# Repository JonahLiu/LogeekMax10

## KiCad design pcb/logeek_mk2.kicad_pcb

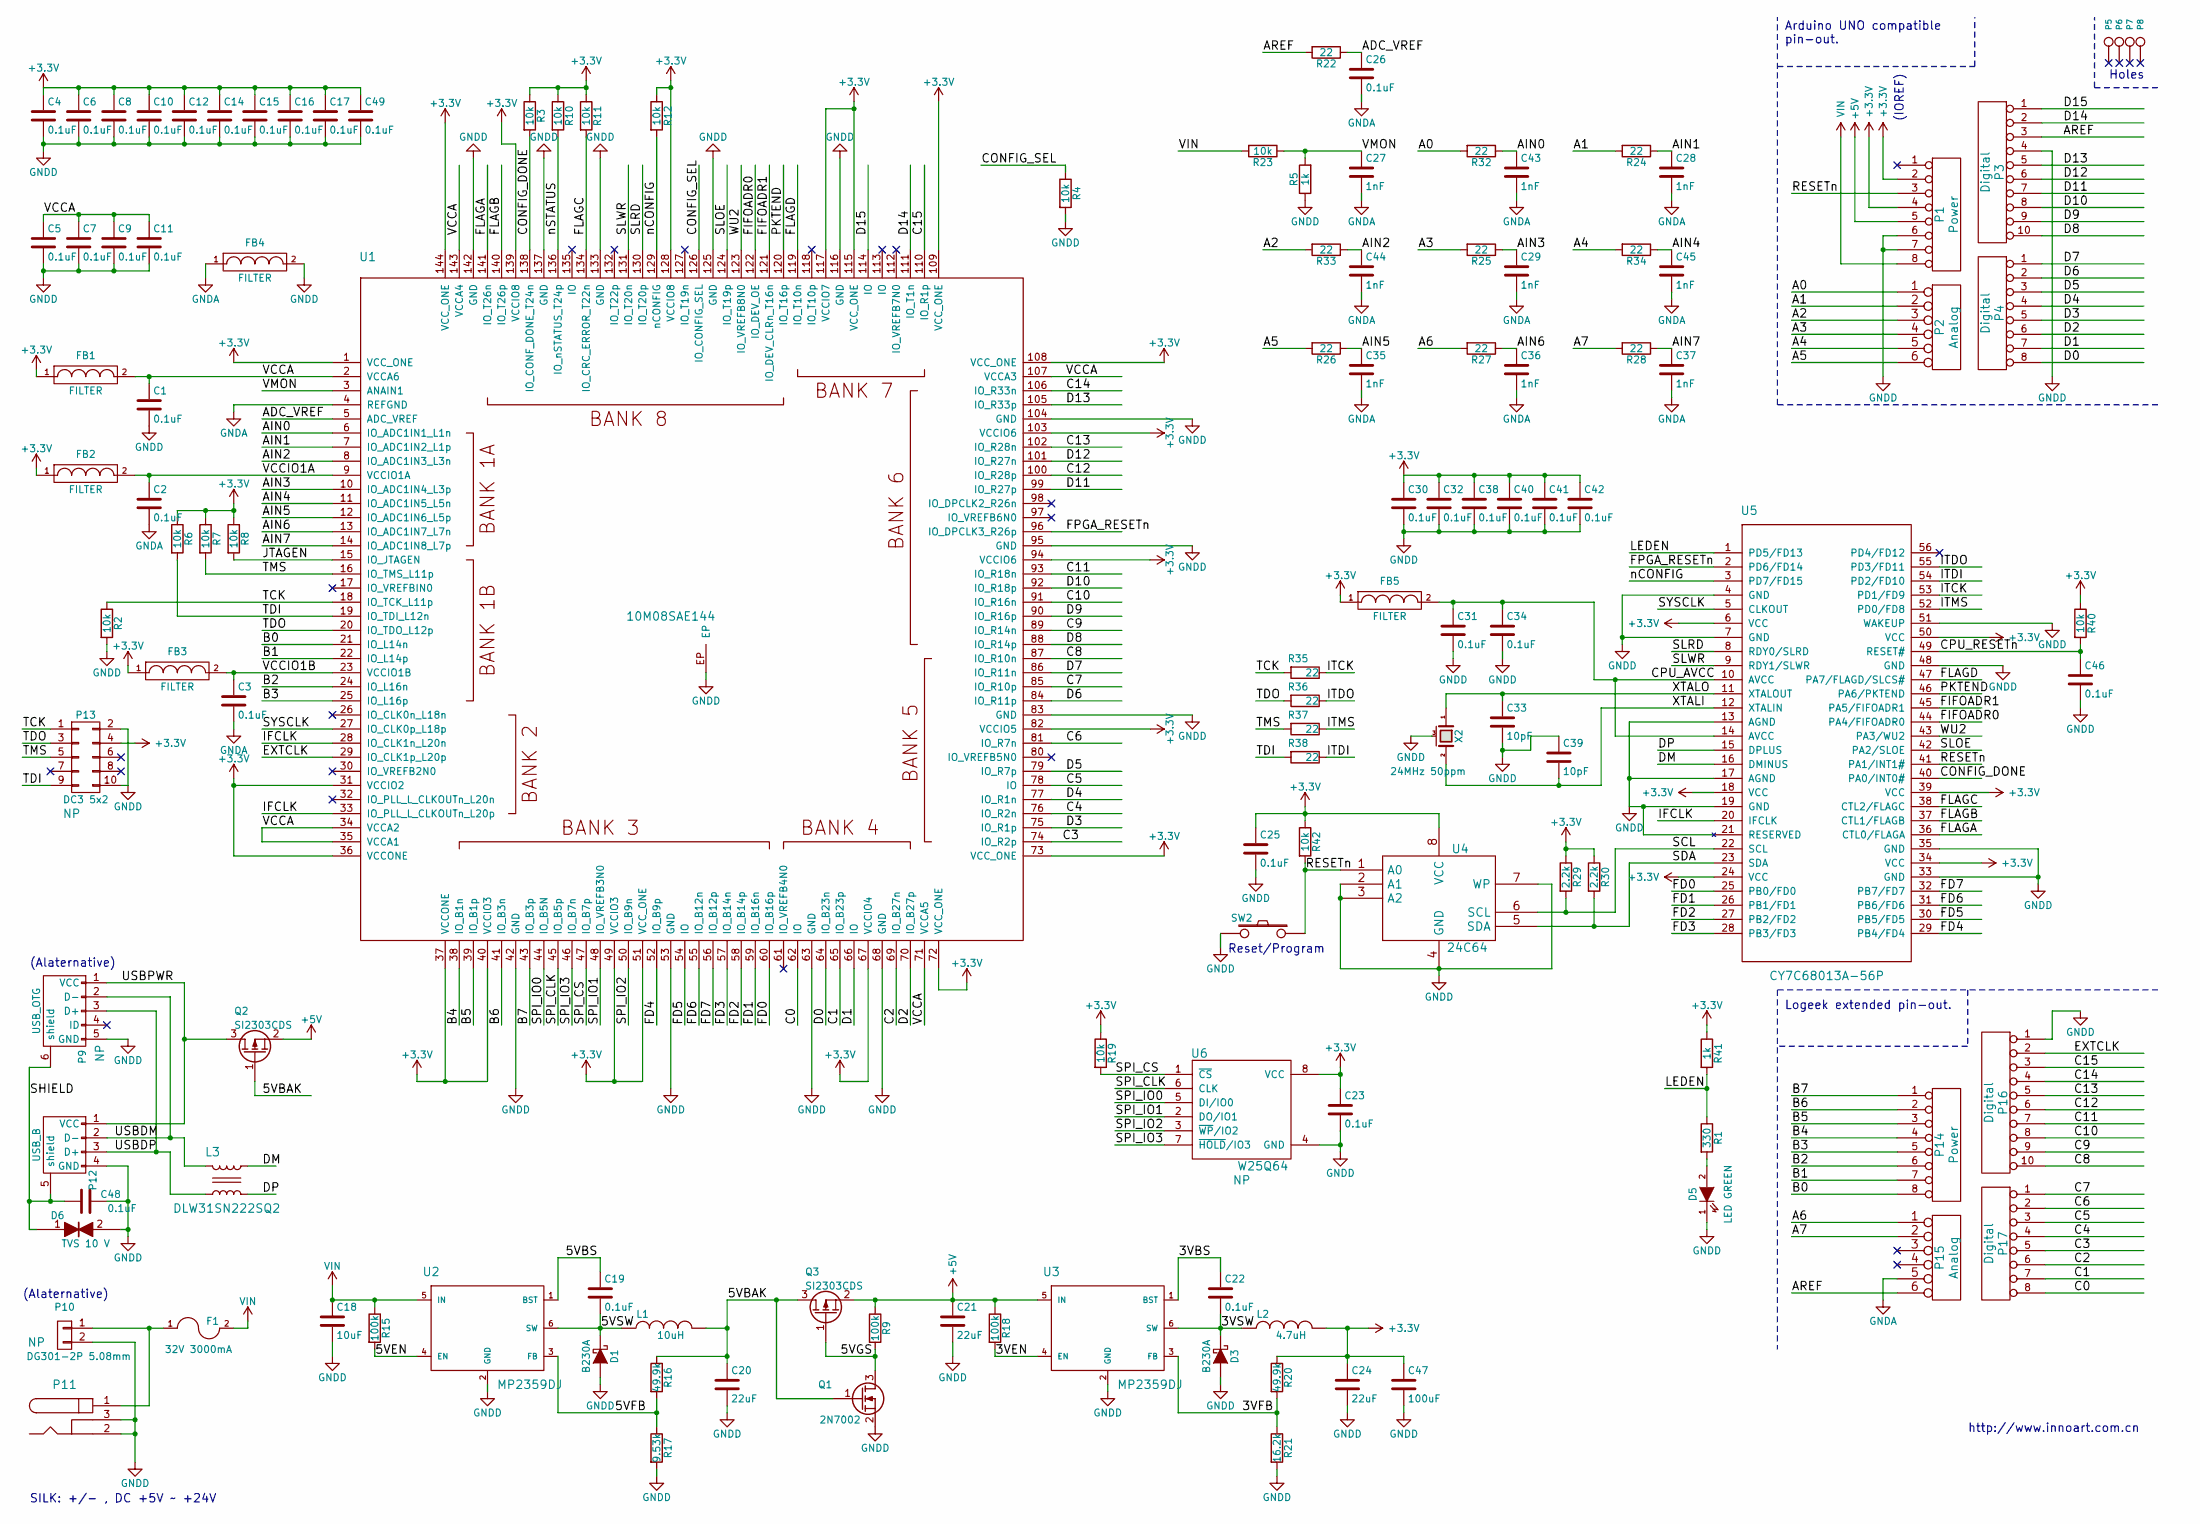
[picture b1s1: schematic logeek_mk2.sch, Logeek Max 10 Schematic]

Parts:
C1, C2, C3, C4, C5, C6, C7, C8, C9, C10, C11, C12, C14, C15, C16, C17, C19, C22, C23, C25, C26, C30, C31, C32, C34, C38, C40, C41, C42, C46, C48, C49: 0.1uF; C_0402
C18: 10uF; C_1206
C20, C21, C24: 22uF; C_0805
C27, C28, C29, C35, C36, C37, C43, C44, C45: 1nF; C_0402
C33, C39: 10pF; C_0402
C47: 100uF; c_elec_5x5.8
D1, D3: B230A; Diode-SMA_Standard
D5: LED GREEN; LED-0603
D6: TVS 10 V; R_0402_HandSoldering
F1: 32V 3000mA; Fuse_SMD1206_Wave
FB1, FB2, FB3, FB4, FB5: FILTER; R_0603
L1: 10uH; Inductor_SM-2020
L2: 4.7uH; Inductor_SM-2020
L3: DLW31SN222SQ2; CommonModeChoke_1206
P1, P14: Power; Socket_Strip_Arduino_1x08
P2, P15: Analog; Socket_Strip_Arduino_1x06
P3, P16: Digital; Socket_Strip_Arduino_1x10
P4, P17: Digital; Socket_Strip_Arduino_1x08
P5, P6, P7, P8: CONN_1; Arduino_1pin
P9: USB_OTG; USB_Micro-B
P10: DG301-2P 5.08mm; DG301_2P_5.08mm_Straight
P11: BARREL_JACK
P12: USB_B
P13: DC3 5x2; Pin_Header_Straight_2x05
Q1: 2N7002; SOT-23
Q2, Q3: SI2303CDS; SOT-23
R1: 330; R_0402_HandSoldering
R2, R3, R4, R6, R7, R8, R10, R11, R12, R19, R23, R40, R42: 10k; R_0402_HandSoldering
R5, R41: 1k; R_0402_HandSoldering
R9, R15, R18: 100k; R_0402_HandSoldering
R16, R20: 49.9k; R_0402_HandSoldering
R17: 9.53k; R_0402_HandSoldering
R21: 16.2k; R_0402_HandSoldering
R22, R24, R25, R26, R27, R28, R32, R33, R34, R35, R36, R37, R38: 22; R_0402_HandSoldering
R29, R30: 2.2k; R_0402_HandSoldering
SW2: PB 4P; SW_SPST_PTS645
U1: 10M08SAE144; TQFP-144EP_20x20mm_Pitch0.5mm
U2, U3: MP2359DJ; SOT-23-6
U4: 24C64; TSSOP-8_4.4x3mm_Pitch0.65mm
U5: CY7C68013A-56P; SSOP-56_7.5x18.5mm_Pitch0.635mm
U6: W25Q64; SOIJ-8_5.3x5.3mm_Pitch1.27mm
X2: 24MHz 50ppm; XTAL3225

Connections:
+3V3: C4.1, C6.1, C8.1, C10.1, C12.1, C14.1, C15.1, C16.1, C17.1, C23.1, C24.1, C25.1, C30.1, C32.1, C38.1, C40.1, C41.1, C42.1, C47.1, C49.1, FB1.1, FB2.1, FB3.1, FB5.1, L2.2, P1.2, P1.4, P13.4, R3.1, R6.1, R7.1, R8.1, R10.1, R11.1, R12.1, R19.1, R20.1, R29.1, R30.1, R40.1, R41.1, R42.1, U1.1 (VCC_ONE), U1.31 (VCCIO2), U1.36 (VCCONE), U1.37 (VCCONE), U1.40 (VCCIO3), U1.49 (VCCIO3), U1.51 (VCC_ONE), U1.67 (VCCIO4), U1.72 (VCC_ONE), U1.73 (VCC_ONE), U1.82 (VCCIO5), U1.94 (VCCIO6), U1.103 (VCCIO6), U1.108 (VCC_ONE), U1.109 (VCC_ONE), U1.115 (VCC_ONE), U1.117 (VCCIO7), U1.128 (VCCIO8), U1.139 (VCCIO8), U1.144 (VCC_ONE), U4.8 (VCC), U5.6 (VCC), U5.18 (VCC), U5.24 (VCC), U5.34 (VCC), U5.39 (VCC), U5.50 (VCC), U6.8 (VCC)
+5V: C21.1, P1.5, Q2.2 (S), Q3.2 (S), R9.1, R18.1, U3.5 (IN)
/3VBS: C22.1, U3.1 (BST)
/3VEN: R18.2, U3.4 (EN)
/3VFB: R20.2, R21.1, U3.3 (FB)
/3VSW: C22.2, D3.1 (K), L2.1, U3.6 (SW)
/5VBAK: C20.1, L1.2, Q1.1 (G), Q2.1 (G), Q3.3 (D), R16.1
/5VBS: C19.1, U2.1 (BST)
/5VEN: R15.2, U2.4 (EN)
/5VFB: R16.2, R17.1, U2.3 (FB)
/5VGS: Q1.3 (D), Q3.1 (G), R9.2
/5VSW: C19.2, D1.1 (K), L1.1, U2.6 (SW)
/A0: P2.1, R32.2
/A1: P2.2, R24.2
/A2: P2.3, R33.2
/A3: P2.4, R25.2
/A4: P2.5, R34.2
/A5: P2.6, R26.2
/A6: P15.1, R27.2
/A7: P15.2, R28.2
/ADC_VREF: C26.1, R22.1, U1.5 (ADC_VREF)
/AIN0: C43.1, R32.1, U1.6 (IO_ADC1IN1_L1n)
/AIN1: C28.1, R24.1, U1.7 (IO_ADC1IN2_L1p)
/AIN2: C44.1, R33.1, U1.8 (IO_ADC1IN3_L3n)
/AIN3: C29.1, R25.1, U1.10 (IO_ADC1IN4_L3p)
/AIN4: C45.1, R34.1, U1.11 (IO_ADC1IN5_L5n)
/AIN5: C35.1, R26.1, U1.12 (IO_ADC1IN6_L5p)
/AIN6: C36.1, R27.1, U1.13 (IO_ADC1IN7_L7n)
/AIN7: C37.1, R28.1, U1.14 (IO_ADC1IN8_L7p)
/AREF: P3.3, P15.6, R22.2
/B0: P14.8, U1.21 (IO_L14n)
/B1: P14.7, U1.22 (IO_L14p)
/B2: P14.6, U1.24 (IO_L16n)
/B3: P14.5, U1.25 (IO_L16p)
/B4: P14.4, U1.38 (IO_B1n)
/B5: P14.3, U1.39 (IO_B1p)
/B6: P14.2, U1.41 (IO_B3n)
/B7: P14.1, U1.43 (IO_B3p)
/C0: P17.8, U1.62 (IO)
/C1: P17.7, U1.65 (IO_B23p)
/C2: P17.6, U1.69 (IO_B27n)
/C3: P17.5, U1.74 (IO_R2p)
/C4: P17.4, U1.76 (IO_R2n)
/C5: P17.3, U1.78 (IO)
/C6: P17.2, U1.81 (IO_R7n)
/C7: P17.1, U1.85 (IO_R10p)
/C8: P16.10, U1.87 (IO_R10n)
/C9: P16.9, U1.89 (IO_R14n)
/C10: P16.8, U1.91 (IO_R16n)
/C11: P16.7, U1.93 (IO_R18n)
/C12: P16.6, U1.100 (IO_R28p)
/C13: P16.5, U1.102 (IO_R28n)
/C14: P16.4, U1.106 (IO_R33n)
/C15: P16.3, U1.110 (IO_R1p)
/CONFIG_DONE: R3.2, U1.138 (IO_CONF_DONE_T24n), U5.40 (PA0/INT0#)
/CONFIG_SEL: R4.1, U1.126 (IO_CONFIG_SEL)
/CPU_AVCC: C31.1, C34.1, FB5.2, U5.10 (AVCC), U5.14 (AVCC)
/CPU_RESETn: C46.1, R40.2, U5.49 (RESET#)
/D0: P4.8, U1.64 (IO_B23n)
/D1: P4.7, U1.66 (IO)
/D2: P4.6, U1.70 (IO_B27p)
/D3: P4.5, U1.75 (IO_R1p)
/D4: P4.4, U1.77 (IO_R1n)
/D5: P4.3, U1.79 (IO_R7p)
/D6: P4.2, U1.84 (IO_R11p)
/D7: P4.1, U1.86 (IO_R11n)
/D8: P3.10, U1.88 (IO_R14p)
/D9: P3.9, U1.90 (IO_R16p)
/D10: P3.8, U1.92 (IO_R18p)
/D11: P3.7, U1.99 (IO_R27p)
/D12: P3.6, U1.101 (IO_R27n)
/D13: P3.5, U1.105 (IO_R33p)
/D14: P3.2, U1.111 (IO_T1n)
/D15: P3.1, U1.114 (IO)
/DM: L3.2, U5.16 (DMINUS)
/DP: L3.3, U5.15 (DPLUS)
/EXTCLK: P16.2, U1.29 (IO_CLK1p_L20p)
/FD0: U1.60 (IO_B16p), U5.25 (PB0/FD0)
/FD1: U1.59 (IO_B16n), U5.26 (PB1/FD1)
/FD2: U1.58 (IO_B14p), U5.27 (PB2/FD2)
/FD3: U1.57 (IO_B14n), U5.28 (PB3/FD3)
/FD4: U1.52 (IO_B9p), U5.29 (PB4/FD4)
/FD5: U1.54 (IO), U5.30 (PB5/FD5)
/FD6: U1.55 (IO_B12n), U5.31 (PB6/FD6)
/FD7: U1.56 (IO_B12p), U5.32 (PB7/FD7)
/FIFOADR0: U1.122 (IO_DEV_OE), U5.44 (PA4/FIFOADR0)
/FIFOADR1: U1.121 (IO_DEV_CLRn_T16n), U5.45 (PA5/FIFOADR1)
/FLAGA: U1.141 (IO_T26n), U5.36 (CTL0/FLAGA)
/FLAGB: U1.140 (IO_T26p), U5.37 (CTL1/FLAGB)
/FLAGC: R11.2, U1.134 (IO_CRC_ERROR_T22n), U5.38 (CTL2/FLAGC)
/FLAGD: U1.119 (IO_T10n), U5.47 (PA7/FLAGD/SLCS#)
/FPGA_RESETn: U1.96 (IO_DPCLK3_R26p), U5.2 (PD6/FD14)
/IFCLK: U1.28 (IO_CLK1n_L20n), U1.33 (IO_PLL_L_CLKOUTn_L20p), U5.20 (IFCLK)
/ITCK: R35.1, U5.53 (PD1/FD9)
/ITDI: R38.1, U5.54 (PD2/FD10)
/ITDO: R36.1, U5.55 (PD3/FD11)
/ITMS: R37.1, U5.52 (PD0/FD8)
/JTAGEN: R8.2, U1.15 (IO_JTAGEN)
/LEDEN: R1.1, R41.2, U5.1 (PD5/FD13)
/PKTEND: U1.120 (IO_T16p), U5.46 (PA6/PKTEND)
/RESETn: P1.3, R42.2, SW2.1, U4.1 (A0), U5.41 (PA1/INT1#)
/SCL: R29.2, U4.6 (SCL), U5.22 (SCL)
/SDA: R30.2, U4.5 (SDA), U5.23 (SDA)
/SHIELD: C48.2, D6.1, P9.6 (shield), P12.5 (shield)
/SLOE: U1.124 (IO_T19p), U5.42 (PA2/SLOE)
/SLRD: U1.130 (IO_T20p), U5.8 (RDY0/SLRD)
/SLWR: U1.131 (IO_T20n), U5.9 (RDY1/SLWR)
/SPI_CLK: U1.45 (IO_B5p), U6.6 (CLK)
/SPI_CS: R19.2, U1.47 (IO_B7p), U6.1 (~CS)
/SPI_IO0: U1.44 (IO_B5N), U6.5 (DI/IO0)
/SPI_IO1: U1.48 (IO_VREFB3N0), U6.2 (DO/IO1)
/SPI_IO2: U1.50 (IO_B9n), U6.3 (~WP~/IO2)
/SPI_IO3: U1.46 (IO_B7n), U6.7 (~HOLD~/IO3)
/SYSCLK: U1.27 (IO_CLK0p_L18p), U5.5 (CLKOUT)
/TCK: P13.1, R2.1, R35.2, U1.18 (IO_TCK_L11p)
/TDI: P13.9, R6.2, R38.2, U1.19 (IO_TDI_L12n)
/TDO: P13.3, R36.2, U1.20 (IO_TDO_L12p)
/TMS: P13.5, R7.2, R37.2, U1.16 (IO_TMS_L11p)
/USBDM: L3.1, P9.2 (D-), P12.2 (D-)
/USBDP: L3.4, P9.3 (D+), P12.3 (D+)
/USBPWR: P9.1 (VCC), P12.1 (VCC), Q2.3 (D)
/VCCA: C1.1, C5.1, C7.1, C9.1, C11.1, FB1.2, U1.2 (VCCA6), U1.34 (VCCA2), U1.35 (VCCA1), U1.71 (VCCA5), U1.107 (VCCA3), U1.143 (VCCA4)
/VCCIO1A: C2.1, FB2.2, U1.9 (VCCIO1A)
/VCCIO1B: C3.1, FB3.2, U1.23 (VCCIO1B)
/VMON: C27.1, R5.2, R23.1, U1.3 (ANAIN1)
/WU2: U1.123 (IO_VREFB8N0), U5.43 (PA3/WU2)
/XTALI: C39.2, U5.12 (XTALIN), X2.2
/XTALO: C33.1, U5.11 (XTALOUT), X2.1
/nCONFIG: R12.2, U1.129 (nCONFIG), U5.3 (PD7/FD15)
/nSTATUS: R10.2, U1.136 (IO_nSTATUS_T24p)
GNDA: C2.2, C3.2, C26.2, C27.2, C28.2, C29.2, C35.2, C36.2, C37.2, C43.2, C44.2, C45.2, FB4.1, P15.5, U1.4 (REFGND)
GNDD: C1.2, C4.2, C5.2, C6.2, C7.2, C8.2, C9.2, C10.2, C11.2, C12.2, C14.2, C15.2, C16.2, C17.2, C18.2, C20.2, C21.2, C23.2, C24.2, C25.2, C30.2, C31.2, C32.2, C33.2, C34.2, C38.2, C39.1, C40.2, C41.2, C42.2, C46.2, C47.2, C48.1, C49.2, D1.2 (A), D3.2 (A), D5.1 (K), D6.2, FB4.2, P1.6, P1.7, P3.4, P9.5 (GND), P10.2, P11.2, P11.3, P12.4 (GND), P13.2, P13.10, P16.1, Q1.2 (S), R2.2, R4.2, R5.1, R17.2, R21.2, SW2.2, U1.42 (GND), U1.53 (GND), U1.63 (GND), U1.68 (GND), U1.83 (GND), U1.95 (GND), U1.104 (GND), U1.116 (GND), U1.125 (GND), U1.133 (GND), U1.137 (GND), U1.142 (GND), U1.EP, U2.2 (GND), U3.2 (GND), U4.2 (A1), U4.3 (A2), U4.4 (GND), U4.7 (WP), U5.4 (GND), U5.7 (GND), U5.13 (AGND), U5.17 (AGND), U5.19 (GND), U5.21 (RESERVED), U5.33 (GND), U5.35 (GND), U5.48 (GND), U5.51 (WAKEUP), U6.4 (GND), X2.3 (case)
unnamed: D5.2 (A), R1.2
unnamed: F1.1, P10.1, P11.1
VIN: C18.1, F1.2, P1.8, R15.1, R23.2, U2.5 (IN)

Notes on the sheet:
Holes
Arduino UNO compatible pin-out.
(Alaternative)
SILK: +/- , DC +5V ~~ +24V
(IOREF)
Logeek extended pin-out.
http://www.innoart.com.cn
Reset/Program

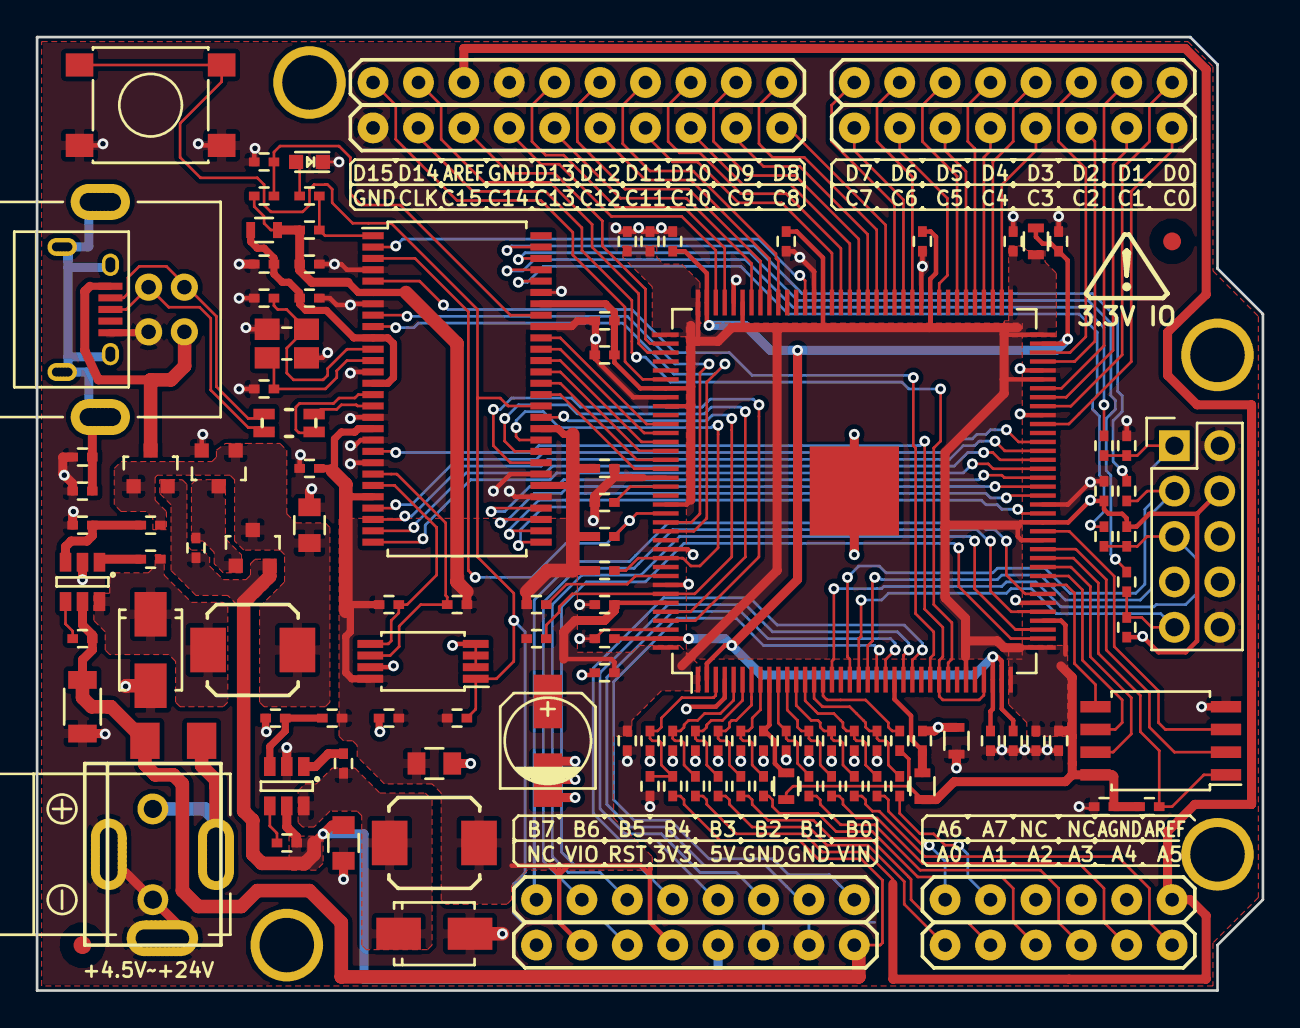
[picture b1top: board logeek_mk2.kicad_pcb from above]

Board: 2 copper layers, 68.6 x 53.3 mm, 129 parts (0 on the bottom side), 135 nets.

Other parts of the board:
FID1, FID2: F; Fiducial_1mm_Dia_2.54mm_Outer_CopperTop

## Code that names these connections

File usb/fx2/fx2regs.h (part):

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
EXTERN xdata _AT_(0xE600) volatile BYTE CPUCS             ;  // Control & Status
EXTERN xdata _AT_(0xE601) volatile BYTE IFCONFIG          ;  // Interface Configuration
EXTERN xdata _AT_(0xE602) volatile BYTE PINFLAGSAB        ;  // FIFO FLAGA and FLAGB Assignments
EXTERN xdata _AT_(0xE603) volatile BYTE PINFLAGSCD        ;  // FIFO FLAGC and FLAGD Assignments
EXTERN xdata _AT_(0xE604) volatile BYTE FIFORESET         ;  // Restore FIFOS to default state
EXTERN xdata _AT_(0xE605) volatile BYTE BREAKPT           ;  // Breakpoint
EXTERN xdata _AT_(0xE606) volatile BYTE BPADDRH           ;  // Breakpoint Address H
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
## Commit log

2015-11-05 Imported source files.
2015-11-05 Part value update.
2015-11-10 Corrected FPGA footprint. Delete extra oscillator. Update silkscreen.
2015-12-06 Updated socket footprints.
2015-12-06 Footprints update.
2015-12-06 Add EXTCLK.
2015-12-06 Analog pin-mapping changed to support VIN monitoring.
2015-12-06 FPGA footprint center pad updated.
2015-12-06 Silkscreen art updated.
2015-12-06 Fine-tune copper and silkscreen. Add a fuse on USB power input.
2015-12-07 Power input socket changed to 5.08mm terminal.
2015-12-07 C14,C15,CLK and GND pins changed.
2015-12-07 Fine-tuned silk art. Gerber generated.
2015-12-20 Power supplies redesigned.
2015-12-22 Updates for better 3D looking.
2015-12-23 Minor footprint change.
2015-12-23 Power switching circuit updated for safety issue.
2015-12-23 Assigned colored 3d model
2015-12-24 Add a fuse to protest against VIN short-circuit.
2015-12-26 Updated 3D shapes
2015-12-28 Updated silk art.
2015-12-28 Final revise before fabrication of Rev.B
2016-01-05 Annotation update.

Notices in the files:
usb/fx2/fx2regs.h:
Code taken from USRP2 firmware (GNU Radio Project), version 3.0.2,
Copyright 2003 Free Software Foundation, Inc.
Copyright (c) 2000 Cypress Semiconductor, All rights reserved
pcb/logeek_mk2.sch:
This is an open source hardware licensed under Creative Commons BY-SA.
